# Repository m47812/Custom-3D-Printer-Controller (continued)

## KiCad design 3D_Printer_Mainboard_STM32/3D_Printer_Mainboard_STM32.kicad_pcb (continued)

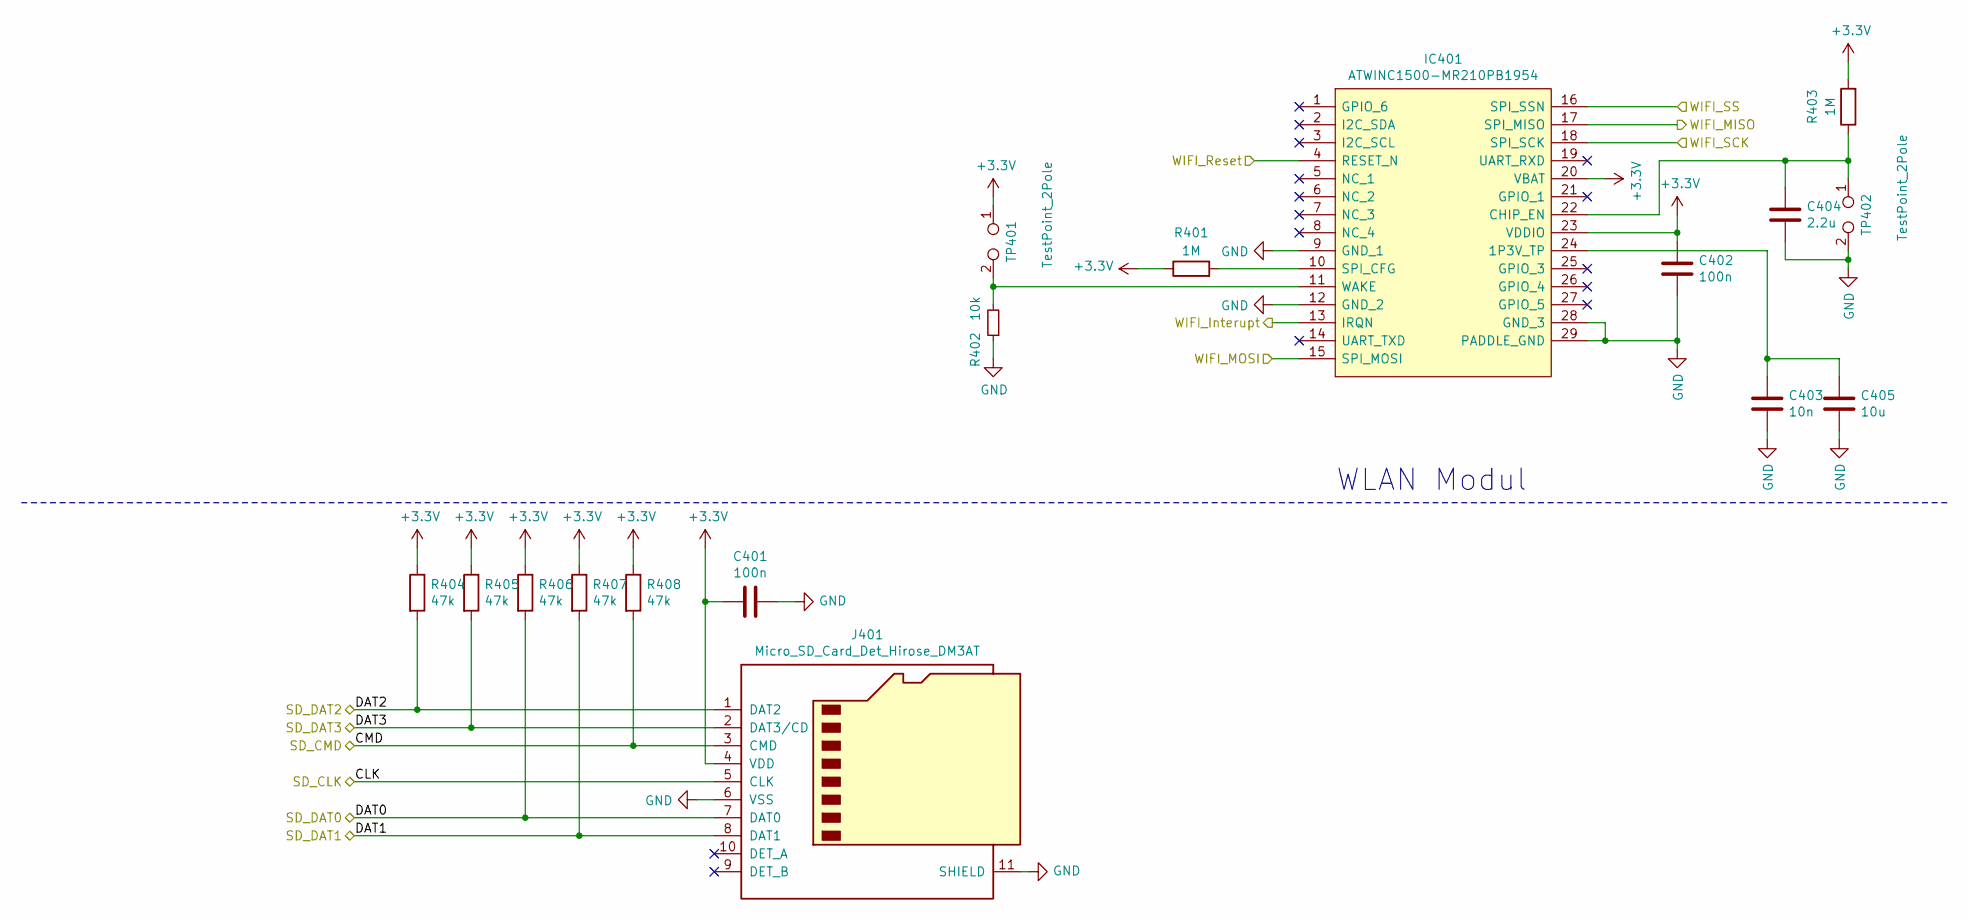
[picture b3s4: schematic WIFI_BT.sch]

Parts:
C401, C402: 100n; C_0402_1005Metric
C403: 10n; C_0402_1005Metric
C404: 2.2u; C_0603_1608Metric
C405: 10u; C_0402_1005Metric
IC401: ATWINC1500-MR210PB1954; ATWINC1500MR210UB1954; Mouser Part Number 579-1500MR210PB1954
J401: Micro_SD_Card_Det_Hirose_DM3AT; microSD_HC_Hirose_DM3D-SF
R401, R403: 1M; R_0402_1005Metric
R402: 10k; R_0402_1005Metric
R404, R405, R406, R407, R408: 47k; R_0402_1005Metric
TP401, TP402: TestPoint_2Pole; PinHeader_1x02_P2.54mm_Vertical

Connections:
+3V3: C401.2, C402.1, IC401.20 (VBAT), IC401.23 (VDDIO), J401.4 (VDD), R401.1, R403.2, R404.1, R405.1, R406.1, R407.1, R408.1, TP401.1; also elsewhere on the board
/64PinControllerversion/MUPI_MISO: IC401.17 (SPI_MISO); also elsewhere on the board
/64PinControllerversion/MUPI_MOSI: IC401.15 (SPI_MOSI); also elsewhere on the board
/64PinControllerversion/MUPI_SCK: IC401.18 (SPI_SCK); also elsewhere on the board
/64PinControllerversion/RESET: IC401.4 (RESET_N); also elsewhere on the board
/64PinControllerversion/SD_CLK: J401.5 (CLK); also elsewhere on the board
/64PinControllerversion/SD_CMD: J401.3 (CMD), R408.2; also elsewhere on the board
/64PinControllerversion/SD_DAT0: J401.7 (DAT0), R406.2; also elsewhere on the board
/64PinControllerversion/SD_DAT1: J401.8 (DAT1), R407.2; also elsewhere on the board
/64PinControllerversion/SD_DAT2: J401.1 (DAT2), R404.2; also elsewhere on the board
/64PinControllerversion/SD_DAT3: J401.2 (DAT3/CD), R405.2; also elsewhere on the board
/64PinControllerversion/WIFI_INTERRUPT: IC401.13 (IRQN); also elsewhere on the board
/64PinControllerversion/WIFI_SEL: IC401.16 (SPI_SSN); also elsewhere on the board
GND: C401.1, C402.2, C403.2, C404.2, C405.2, IC401.9 (GND_1), IC401.12 (GND_2), IC401.28 (GND_3), IC401.29 (PADDLE_GND), J401.6 (VSS), J401.11 (SHIELD), R402.1, TP402.2; also elsewhere on the board
unnamed: C403.1, C405.1, IC401.24 (1P3V_TP)
unnamed: C404.1, IC401.22 (CHIP_EN), R403.1, TP402.1
unnamed: IC401.10 (SPI_CFG), R401.2
unnamed: IC401.11 (WAKE), R402.2, TP401.2

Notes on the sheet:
WLAN Modul

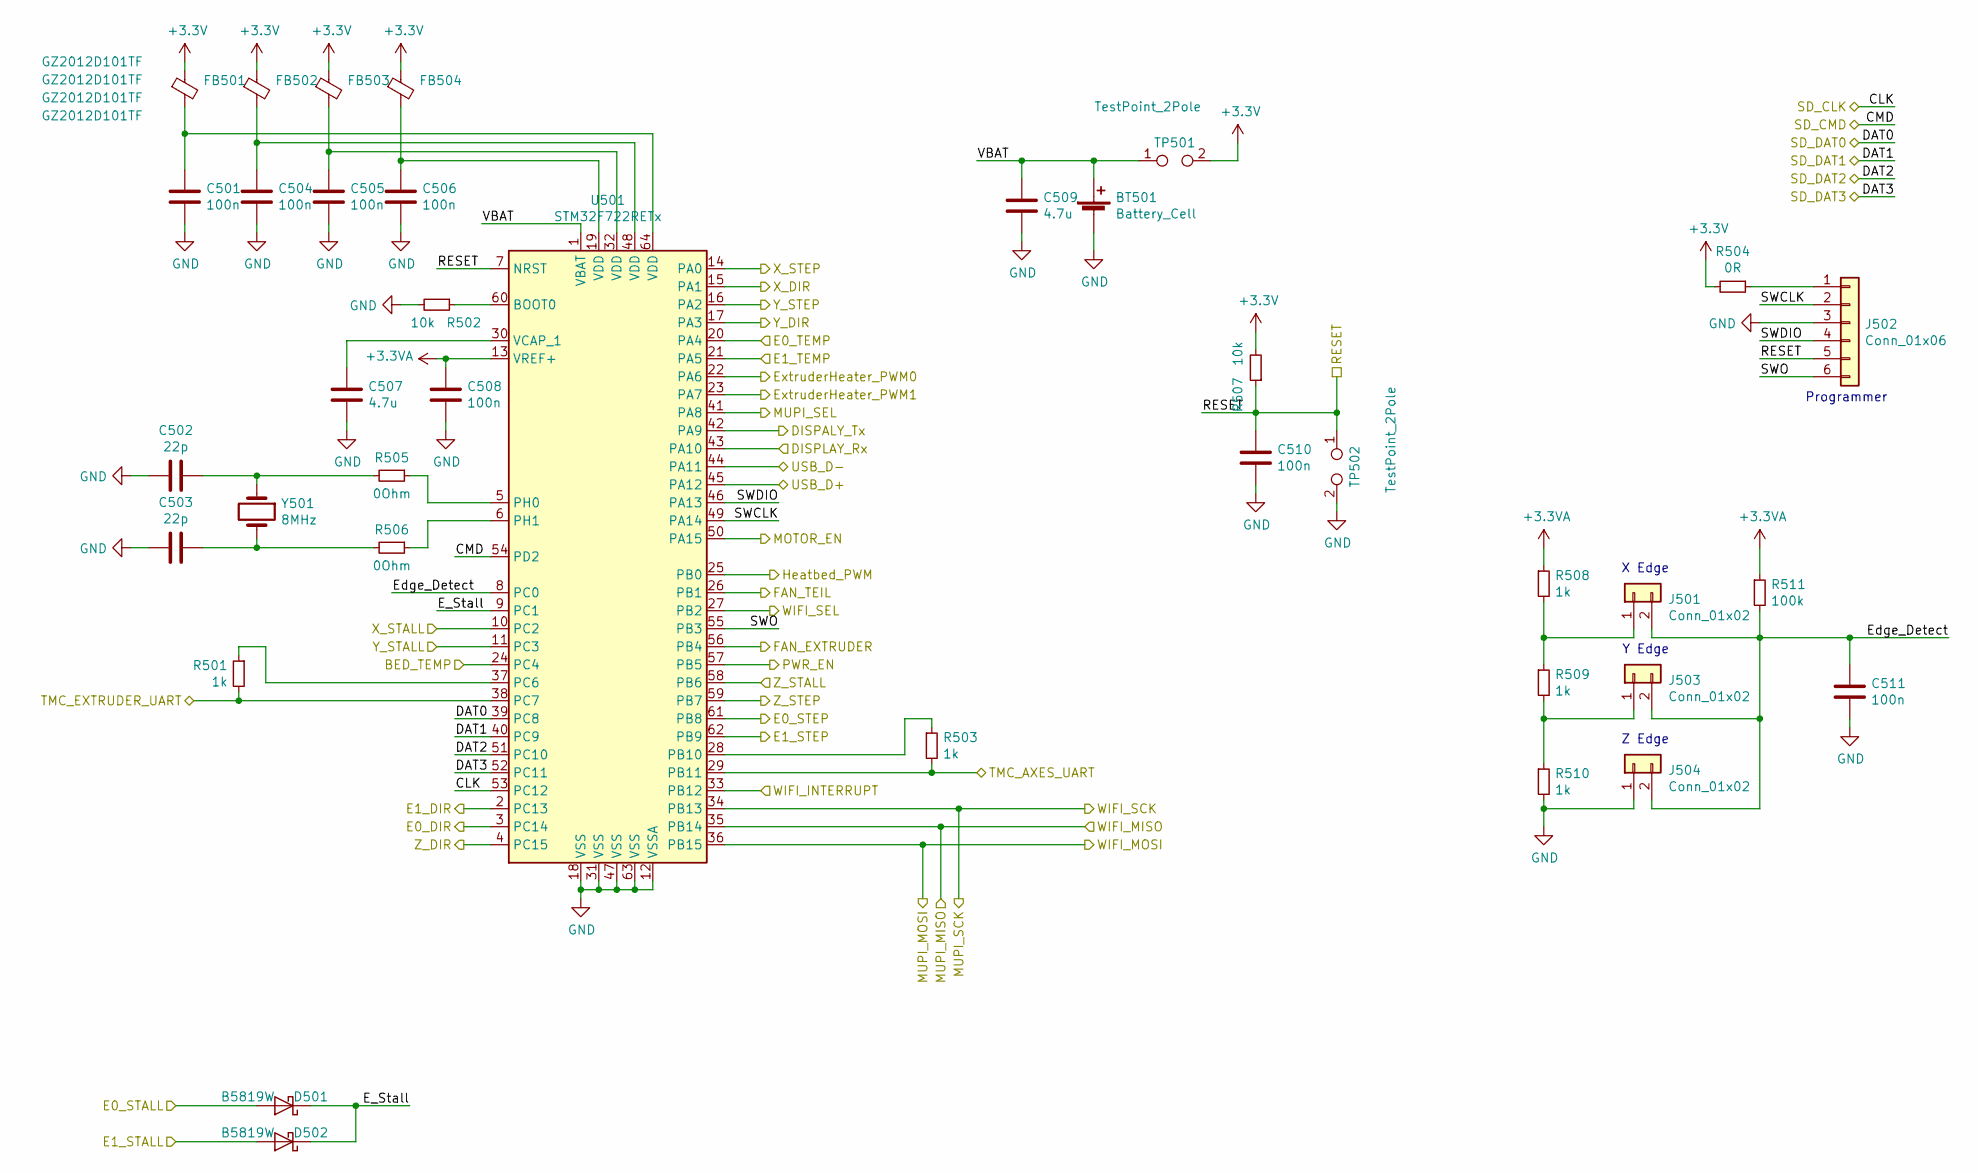
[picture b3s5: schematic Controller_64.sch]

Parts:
BT501: Battery_Cell; BatteryHolder_Keystone_1058_1x2032
C501, C504, C505, C506, C508, C510, C511: 100n; C_0402_1005Metric
C502, C503: 22p; C_0402_1005Metric
C507, C509: 4.7u; C_0603_1608Metric
D501, D502: B5819W; D_SOD-123
FB501, FB502, FB503, FB504: GZ2012D101TF; R_0805_2012Metric
J501, J503, J504: Conn_01x02; Molex_KK-254_AE-6410-02A_1x02_P2.54mm_Vertical
J502: Conn_01x06; PinHeader_1x06_P2.54mm_Vertical
R501, R503, R508, R509, R510: 1k; R_0402_1005Metric
R502, R507: 10k; R_0402_1005Metric
R504: 0R; R_0603_1608Metric_Pad1.05x0.95mm_HandSolder
R505, R506: 0Ohm; R_0603_1608Metric
R511: 100k; R_0402_1005Metric
TP501, TP502: TestPoint_2Pole; PinHeader_1x02_P2.54mm_Vertical
U501: STM32F722RETx; LQFP-64_10x10mm_P0.5mm
Y501: 8MHz; Crystal_SMD_5032-2Pin_5.0x3.2mm

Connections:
+3.3VA: C508.1, R508.1, R511.1, U501.13 (VREF+); also elsewhere on the board
+3V3: FB501.1, FB502.1, FB503.1, FB504.1, R504.2, R507.2, TP501.2; also elsewhere on the board
/64PinControllerversion/BED_TEMP: U501.24 (PC4); also elsewhere on the board
/64PinControllerversion/DISPALY_Tx: U501.42 (PA9); also elsewhere on the board
/64PinControllerversion/E0_DIR: U501.3 (PC14); also elsewhere on the board
/64PinControllerversion/E0_STEP: U501.61 (PB8); also elsewhere on the board
/64PinControllerversion/E0_TEMP: U501.20 (PA4); also elsewhere on the board
/64PinControllerversion/E1_DIR: U501.2 (PC13); also elsewhere on the board
/64PinControllerversion/E1_STEP: U501.62 (PB9); also elsewhere on the board
/64PinControllerversion/E1_TEMP: U501.21 (PA5); also elsewhere on the board
/64PinControllerversion/E_Stall: D501.1 (K), D502.1 (K), U501.9 (PC1)
/64PinControllerversion/Edge_Detect: C511.1, J501.2, J503.2, J504.2, R511.2, U501.8 (PC0)
/64PinControllerversion/FAN_TEIL: U501.26 (PB1); also elsewhere on the board
/64PinControllerversion/MOTOR_EN: U501.50 (PA15); also elsewhere on the board
/64PinControllerversion/MUPI_MISO: U501.35 (PB14); also elsewhere on the board
/64PinControllerversion/MUPI_MOSI: U501.36 (PB15); also elsewhere on the board
/64PinControllerversion/MUPI_SCK: U501.34 (PB13); also elsewhere on the board
/64PinControllerversion/MUPI_SEL: U501.41 (PA8); also elsewhere on the board
/64PinControllerversion/PWR_EN: U501.57 (PB5); also elsewhere on the board
/64PinControllerversion/RESET: C510.1, J502.5, R507.1, TP502.1, U501.7 (NRST); also elsewhere on the board
/64PinControllerversion/SD_CLK: U501.53 (PC12); also elsewhere on the board
/64PinControllerversion/SD_CMD: U501.54 (PD2); also elsewhere on the board
/64PinControllerversion/SD_DAT0: U501.39 (PC8); also elsewhere on the board
/64PinControllerversion/SD_DAT1: U501.40 (PC9); also elsewhere on the board
/64PinControllerversion/SD_DAT2: U501.51 (PC10); also elsewhere on the board
/64PinControllerversion/SD_DAT3: U501.52 (PC11); also elsewhere on the board
/64PinControllerversion/SWCLK: J502.2, U501.49 (PA14)
/64PinControllerversion/SWDIO: J502.4, U501.46 (PA13)
/64PinControllerversion/SWO: J502.6, U501.55 (PB3)
/64PinControllerversion/TMC_AXES_UART: R503.2, U501.29 (PB11); also elsewhere on the board
/64PinControllerversion/TMC_EXTRUDER_UART: R501.2, U501.38 (PC7); also elsewhere on the board
/64PinControllerversion/USB_D+: U501.45 (PA12); also elsewhere on the board
/64PinControllerversion/USB_D-: U501.44 (PA11); also elsewhere on the board
/64PinControllerversion/VBAT: BT501.1 (+), C509.1, TP501.1, U501.1 (VBAT)
/64PinControllerversion/WIFI_INTERRUPT: U501.33 (PB12); also elsewhere on the board
/64PinControllerversion/WIFI_SEL: U501.27 (PB2); also elsewhere on the board
/64PinControllerversion/X_DIR: U501.15 (PA1); also elsewhere on the board
/64PinControllerversion/X_STEP: U501.14 (PA0); also elsewhere on the board
/64PinControllerversion/Y_DIR: U501.17 (PA3); also elsewhere on the board
/64PinControllerversion/Y_STEP: U501.16 (PA2); also elsewhere on the board
/64PinControllerversion/Z_DIR: U501.4 (PC15); also elsewhere on the board
/64PinControllerversion/Z_STEP: U501.59 (PB7); also elsewhere on the board
/Fans & Heater/EXT_A_EN: U501.22 (PA6); also elsewhere on the board
/Fans & Heater/EXT_B_EN: U501.23 (PA7); also elsewhere on the board
/Fans & Heater/Extruderfan: U501.56 (PB4); also elsewhere on the board
/Fans & Heater/Heatbed_EN: U501.25 (PB0); also elsewhere on the board
/MUPI Connector & Display/DISPLAY_IN_RX: U501.43 (PA10); also elsewhere on the board
/Stepperdrivers/E0_DRIVER_STALL: D501.2 (A); also elsewhere on the board
/Stepperdrivers/E1_DRIVER_STALL: D502.2 (A); also elsewhere on the board
/Stepperdrivers/X_DRIVER_STALL: U501.10 (PC2); also elsewhere on the board
/Stepperdrivers/Y_DRIVER_STALL: U501.11 (PC3); also elsewhere on the board
/Stepperdrivers/Z_DRIVER_STALL: U501.58 (PB6); also elsewhere on the board
GND: BT501.2 (-), C501.1, C502.2, C503.2, C504.1, C505.1, C506.1, C507.2, C508.2, C509.2, C510.2, C511.2, J502.3, J504.1, R502.2, R510.2, TP502.2, U501.12 (VSSA), U501.18 (VSS), U501.31 (VSS), U501.47 (VSS), U501.63 (VSS); also elsewhere on the board
unnamed: C501.2, FB501.2, U501.64 (VDD)
unnamed: C502.1, R505.2, Y501.1
unnamed: C503.1, R506.2, Y501.2
unnamed: C504.2, FB502.2, U501.48 (VDD)
unnamed: C505.2, FB503.2, U501.32 (VDD)
unnamed: C506.2, FB504.2, U501.19 (VDD)
unnamed: C507.1, U501.30 (VCAP_1)
unnamed: J501.1, R508.2, R509.1
unnamed: J502.1, R504.1
unnamed: J503.1, R509.2, R510.1
unnamed: R501.1, U501.37 (PC6)
unnamed: R502.1, U501.60 (BOOT0)
unnamed: R503.1, U501.28 (PB10)
unnamed: R505.1, U501.5 (PH0)
unnamed: R506.1, U501.6 (PH1)

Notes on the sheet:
Programmer
X Edge
Y Edge
Z Edge

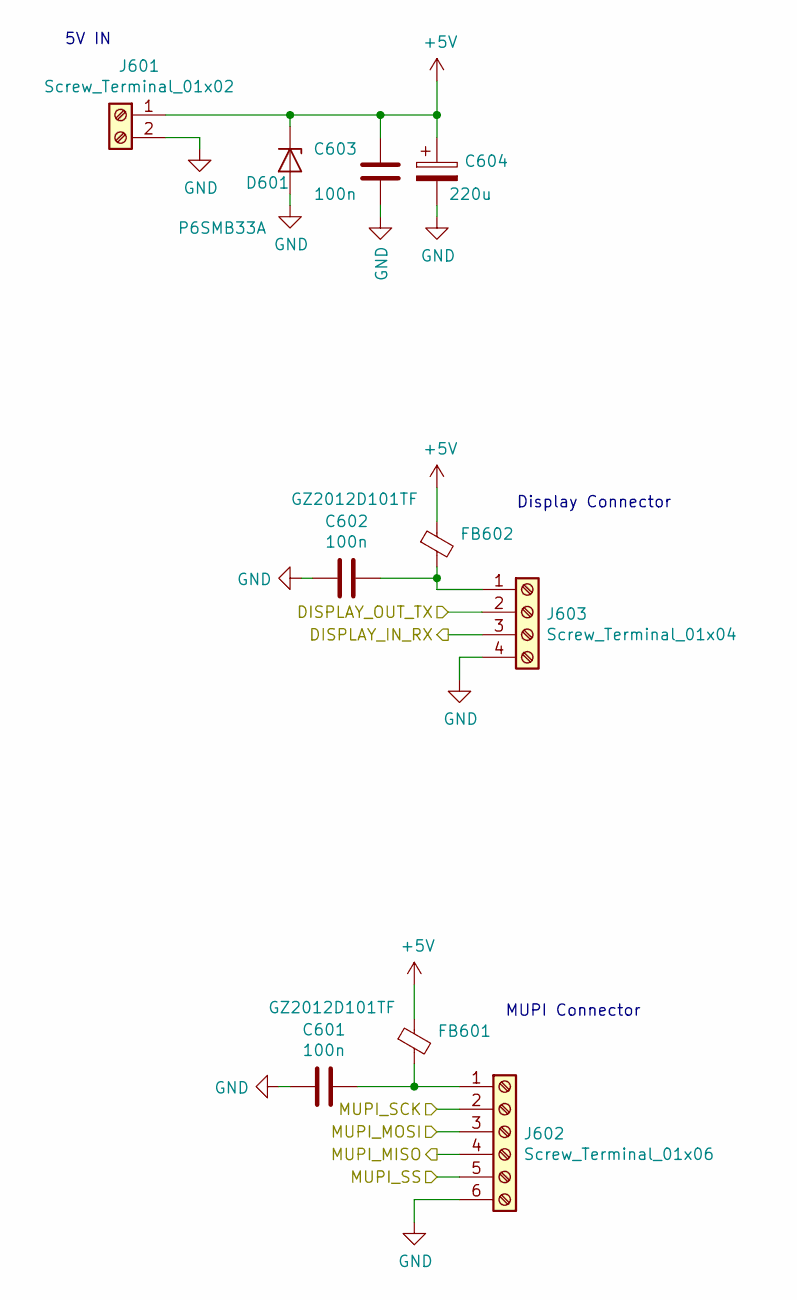
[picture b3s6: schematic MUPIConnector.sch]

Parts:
C601, C602, C603: 100n; C_0603_1608Metric
C604: 220u; CP_Elec_8x10
D601: P6SMB33A; D_SMB
FB601, FB602: GZ2012D101TF; R_0805_2012Metric
J601: Screw_Terminal_01x02; TerminalBlock_Phoenix_MPT-0,5-2-2.54_1x02_P2.54mm_Horizontal
J602: Screw_Terminal_01x06; TerminalBlock_Phoenix_MPT-0,5-6-2.54_1x06_P2.54mm_Horizontal
J603: Screw_Terminal_01x04; TerminalBlock_Phoenix_MPT-0,5-4-2.54_1x04_P2.54mm_Horizontal

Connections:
+5V: C603.1, C604.1, D601.1 (K), FB601.1, FB602.1, J601.1
/64PinControllerversion/DISPALY_Tx: J603.2; also elsewhere on the board
/64PinControllerversion/MUPI_MISO: J602.4; also elsewhere on the board
/64PinControllerversion/MUPI_MOSI: J602.3; also elsewhere on the board
/64PinControllerversion/MUPI_SCK: J602.2; also elsewhere on the board
/64PinControllerversion/MUPI_SEL: J602.5; also elsewhere on the board
/MUPI Connector & Display/DISPLAY_IN_RX: J603.3; also elsewhere on the board
GND: C601.2, C602.2, C603.2, C604.2, D601.2 (A), J601.2, J602.6, J603.4; also elsewhere on the board
unnamed: C601.1, FB601.2, J602.1
unnamed: C602.1, FB602.2, J603.1

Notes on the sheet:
MUPI Connector
Display Connector
5V IN

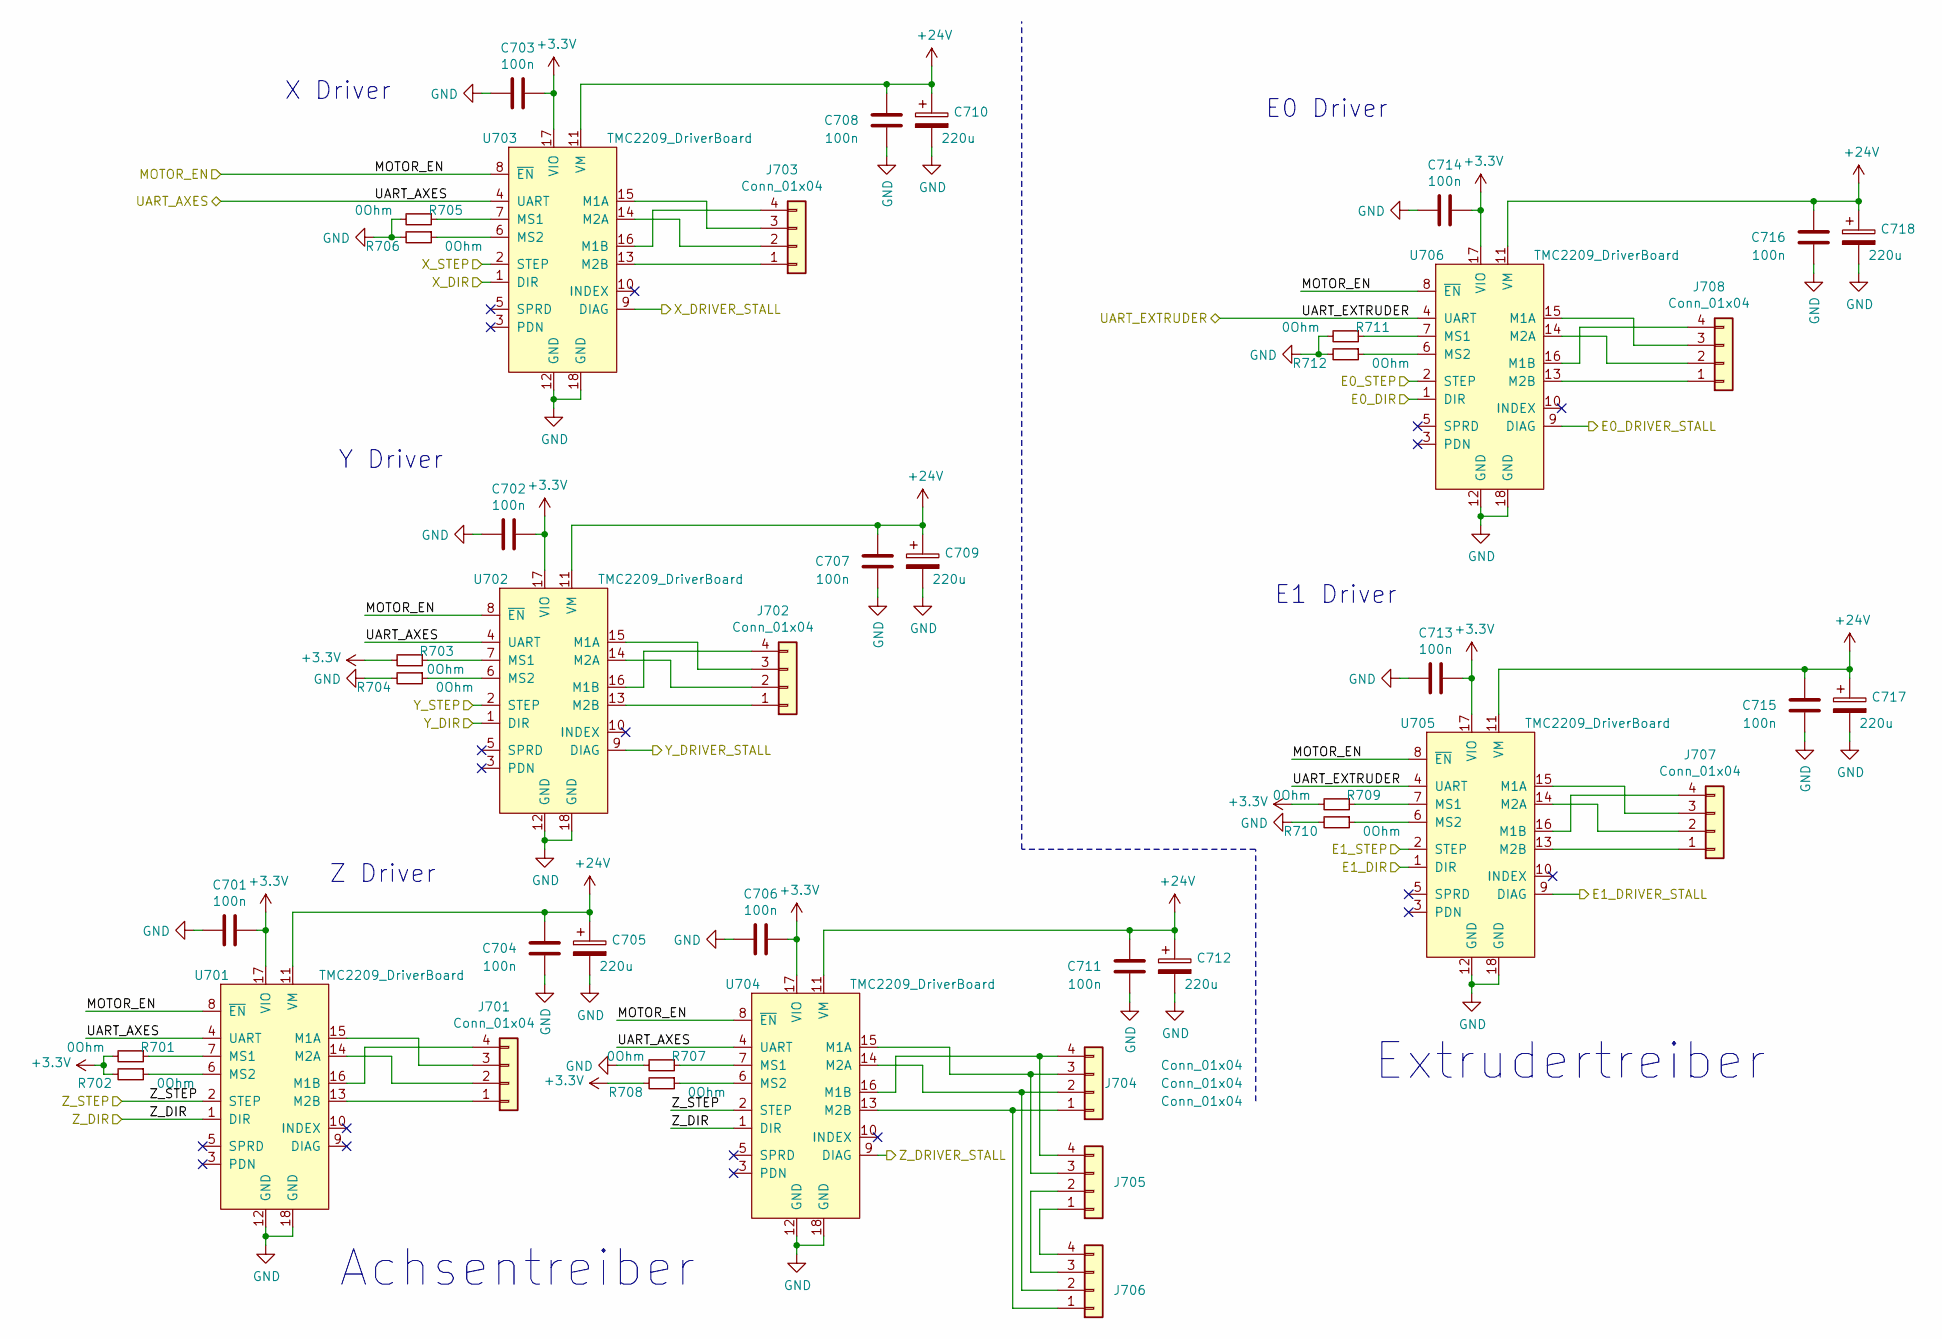
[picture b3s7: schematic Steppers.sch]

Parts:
C701, C702, C703, C704, C706, C707, C708, C711, C713, C714, C715, C716: 100n; C_0603_1608Metric
C705, C709, C710, C712, C717, C718: 220u; CP_Elec_8x10
J701, J702, J703, J704, J705, J706, J707, J708: Conn_01x04; Molex_KK-254_AE-6410-04A_1x04_P2.54mm_Vertical
R701, R702, R703, R704, R705, R706, R707, R708, R709, R710, R711, R712: 0Ohm; R_0603_1608Metric
U701, U702, U703, U704, U705, U706: TMC2209_DriverBoard

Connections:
+3V3: C701.1, C702.1, C703.1, C706.1, C713.1, C714.1, R701.2, R702.2, R703.2, R708.2, R709.2, U701.17 (VIO), U702.17 (VIO), U703.17 (VIO), U704.17 (VIO), U705.17 (VIO), U706.17 (VIO); also elsewhere on the board
+24V: C704.1, C705.1, C707.1, C708.1, C709.1, C710.1, C711.1, C712.1, C715.1, C716.1, C717.1, C718.1, U701.11 (VM), U702.11 (VM), U703.11 (VM), U704.11 (VM), U705.11 (VM), U706.11 (VM); also elsewhere on the board
/64PinControllerversion/E0_DIR: U706.1 (DIR); also elsewhere on the board
/64PinControllerversion/E0_STEP: U706.2 (STEP); also elsewhere on the board
/64PinControllerversion/E1_DIR: U705.1 (DIR); also elsewhere on the board
/64PinControllerversion/E1_STEP: U705.2 (STEP); also elsewhere on the board
/64PinControllerversion/MOTOR_EN: U701.8 (~EN), U702.8 (~EN), U703.8 (~EN), U704.8 (~EN), U705.8 (~EN), U706.8 (~EN); also elsewhere on the board
/64PinControllerversion/TMC_AXES_UART: U701.4 (UART), U702.4 (UART), U703.4 (UART), U704.4 (UART); also elsewhere on the board
/64PinControllerversion/TMC_EXTRUDER_UART: U705.4 (UART), U706.4 (UART); also elsewhere on the board
/64PinControllerversion/X_DIR: U703.1 (DIR); also elsewhere on the board
/64PinControllerversion/X_STEP: U703.2 (STEP); also elsewhere on the board
/64PinControllerversion/Y_DIR: U702.1 (DIR); also elsewhere on the board
/64PinControllerversion/Y_STEP: U702.2 (STEP); also elsewhere on the board
/64PinControllerversion/Z_DIR: U701.1 (DIR), U704.1 (DIR); also elsewhere on the board
/64PinControllerversion/Z_STEP: U701.2 (STEP), U704.2 (STEP); also elsewhere on the board
/Stepperdrivers/E0_DRIVER_STALL: U706.9 (DIAG); also elsewhere on the board
/Stepperdrivers/E1_DRIVER_STALL: U705.9 (DIAG); also elsewhere on the board
/Stepperdrivers/X_DRIVER_STALL: U703.9 (DIAG); also elsewhere on the board
/Stepperdrivers/Y_DRIVER_STALL: U702.9 (DIAG); also elsewhere on the board
/Stepperdrivers/Z_DRIVER_STALL: U704.9 (DIAG); also elsewhere on the board
GND: C701.2, C702.2, C703.2, C704.2, C705.2, C706.2, C707.2, C708.2, C709.2, C710.2, C711.2, C712.2, C713.2, C714.2, C715.2, C716.2, C717.2, C718.2, R704.2, R705.2, R706.2, R707.2, R710.2, R711.2, R712.2, U701.12 (GND), U701.18 (GND), U702.12 (GND), U702.18 (GND), U703.12 (GND), U703.18 (GND), U704.12 (GND), U704.18 (GND), U705.12 (GND), U705.18 (GND), U706.12 (GND), U706.18 (GND); also elsewhere on the board
unnamed: J701.1, U701.13 (M2B)
unnamed: J701.2, U701.14 (M2A)
unnamed: J701.3, U701.15 (M1A)
unnamed: J701.4, U701.16 (M1B)
unnamed: J702.1, U702.13 (M2B)
unnamed: J702.2, U702.14 (M2A)
unnamed: J702.3, U702.15 (M1A)
unnamed: J702.4, U702.16 (M1B)
unnamed: J703.1, U703.13 (M2B)
unnamed: J703.2, U703.14 (M2A)
unnamed: J703.3, U703.15 (M1A)
unnamed: J703.4, U703.16 (M1B)
unnamed: J704.1, J706.1, U704.13 (M2B)
unnamed: J704.2, J706.2, U704.14 (M2A)
unnamed: J704.3, J705.3, U704.15 (M1A)
unnamed: J704.4, J705.4, U704.16 (M1B)
unnamed: J705.1, J706.4
unnamed: J705.2, J706.3
unnamed: J707.1, U705.13 (M2B)
unnamed: J707.2, U705.14 (M2A)
unnamed: J707.3, U705.15 (M1A)
unnamed: J707.4, U705.16 (M1B)
unnamed: J708.1, U706.13 (M2B)
unnamed: J708.2, U706.14 (M2A)
unnamed: J708.3, U706.15 (M1A)
unnamed: J708.4, U706.16 (M1B)
unnamed: R701.1, U701.7 (MS1)
unnamed: R702.1, U701.6 (MS2)
unnamed: R703.1, U702.7 (MS1)
unnamed: R704.1, U702.6 (MS2)
unnamed: R705.1, U703.7 (MS1)
unnamed: R706.1, U703.6 (MS2)
unnamed: R707.1, U704.7 (MS1)
unnamed: R708.1, U704.6 (MS2)
unnamed: R709.1, U705.7 (MS1)
unnamed: R710.1, U705.6 (MS2)
unnamed: R711.1, U706.7 (MS1)
unnamed: R712.1, U706.6 (MS2)

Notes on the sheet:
Achsentreiber
Extrudertreiber
X Driver
Y Driver
E0 Driver
E1 Driver
Z Driver

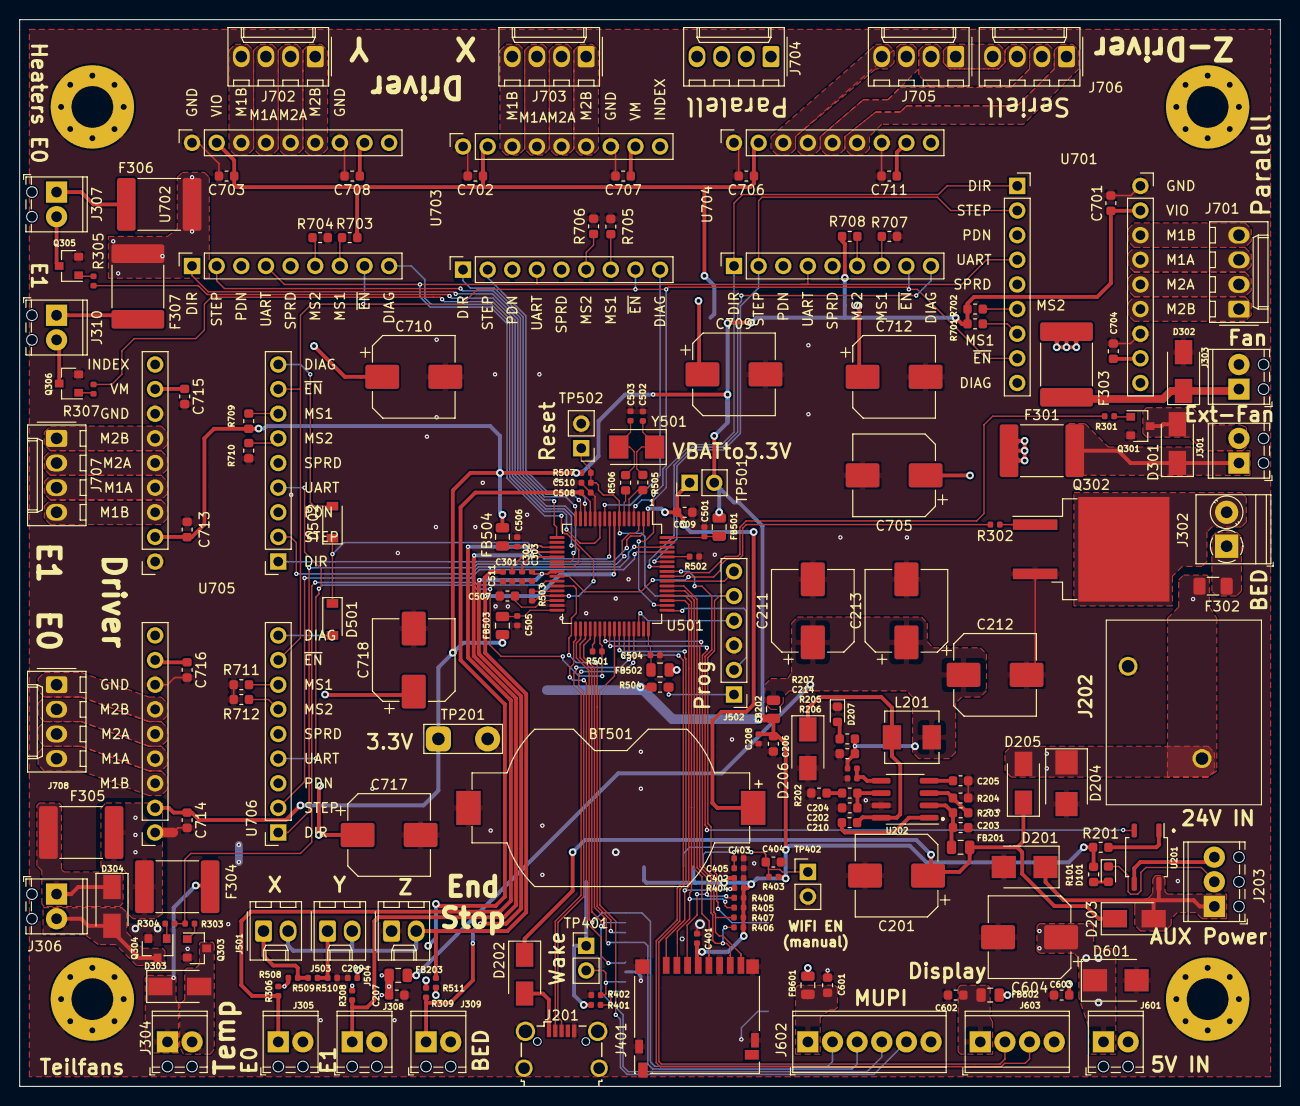
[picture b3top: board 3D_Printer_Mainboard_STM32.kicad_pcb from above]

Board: 2 copper layers, 130.0 x 110.0 mm, 191 parts (1 on the bottom side), 150 nets.

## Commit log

2022-04-30 Added Mainboard Files
2022-04-30 Motor Driver
2022-04-30 Added Handheld files
2022-04-30 Components List
2022-04-30 Create LICENSE
2022-04-30 Re-located Images
